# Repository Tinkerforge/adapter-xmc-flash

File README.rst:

XMC Flash Adapter
=================

This repository contains the firmware source code and the hardware design
files. The documentation generator configs can be found at
https://github.com/Tinkerforge/generators

Repository Content
------------------

software/:
 * examples/: Examples for all supported languages
 * build/: Makefile and compiled files
 * src/: Source code of firmware
 * generate_makefile: Shell script to generate Makefile from cmake script

hardware/:
 * Contains kicad project files and additionally schematics as pdf

datasheets/:
 * Contains datasheets for sensors and complex ICs that are used

Hardware
--------

The hardware is designed with the open source EDA Suite KiCad
(http://www.kicad.org). Before you are able to open the files,
you have to install the Tinkerforge kicad-libraries
(https://github.com/Tinkerforge/kicad-libraries). You can either clone
them directly in hardware/ or clone them in a separate folder and
symlink them into hardware/
(ln -s kicad_path/kicad-libraries project_path/hardware). After that you
can open the .pro file in hardware/ with kicad and from there view and
modify the schematics and the PCB layout.

Software
--------

To compile the c code we recommend you to install the newest CodeSourcery arm
eabi gcc compiler
(http://www.codesourcery.com/sgpp/lite/arm/portal/subscription?@template=lite).
You also need to install bricklib (https://github.com/Tinkerforge/bricklib)
and brickletlib (https://github.com/Tinkerforge/brickletlib).
You can either clone them directly in software/src/ or clone them in a
separate folder and symlink them into software/src/
(ln -s bricklib_path/bricklib project_path/software/src/).

After that you can generate a Makefile from the cmake script with the
generate_makefile shell script (in software/) and build the firmware
by invoking make in software/build/. The firmware (.bin) can then be found
in software/build/ and uploaded with brickv (click button "Flashing"
on start screen).

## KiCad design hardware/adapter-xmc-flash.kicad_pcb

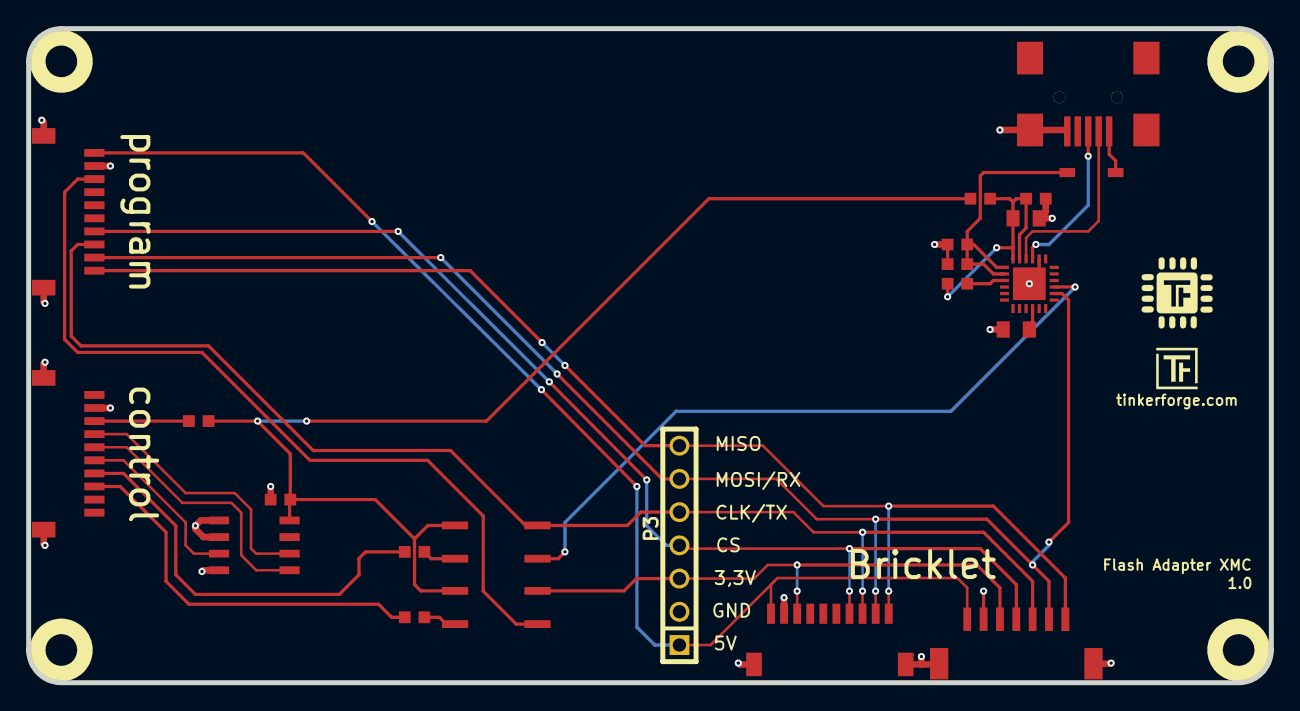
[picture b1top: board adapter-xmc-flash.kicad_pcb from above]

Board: 2 copper layers, 95.0 x 50.0 mm, 26 parts (0 on the bottom side), 25 nets.

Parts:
C1, C2, C5, C6: 100n; C0603F
C3, C4: 4.7µF/10V; C0805
D1: B0520LW; SOD-123
J1: USB-MINI-B-SMD
P1, P4, P5: CON-SENSOR
P2: CON-SENSOR2
P3: CONN_01X07; PIN_ARRAY-7X1
R1: 4k7; R0603F
R2: DNP; R0603F
R3: 0; R0603F
R4, R5: 1k; R0603F
U1: CP2104; QFN-24-4x4-EP
U2: M24C64; SOIC8
U3, U4: CPC1020N; SOP4-WIDE
U5, U6, U7, U8: DRILL; DRILL_NP

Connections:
3V3: C6.1, R2.1, R3.1, U2.8, U3.1, U4.1
GND: C1.2, C2.2, C3.2, C4.2, C5.2, C6.2, J1.5, J1.6, P1.2, P1.EP, P2.2, P2.EP, P3.2, P4.2, P4.EP, P5.2, P5.EP, U1.2, U1.25, U2.1, U2.2, U2.4
unnamed: C1.1, C2.1, D1.2, U1.7, U1.8
unnamed: C3.1, U1.16
unnamed: C4.1, C5.1, R1.1, R2.2, U1.5, U1.6
unnamed: D1.1, J1.1
unnamed: J1.2, U1.4
unnamed: J1.3, U1.3
unnamed: P1.1, P2.1, P3.1, P4.1
unnamed: P1.7, P2.4, P3.4, P4.7
unnamed: P1.10, P2.7, P3.7, P4.10
unnamed: P5.3, R3.2
unnamed: P5.4, U2.6
unnamed: P5.5, U2.5
unnamed: P5.6, U2.3
unnamed: P5.7, R4.2
unnamed: P5.8, R5.2
unnamed: R1.2, U1.9
unnamed: R4.1, U4.2
unnamed: R5.1, U3.2
POWER_RIN: P4.3, U3.3
POWER_ROUT: P1.3, P2.3, P3.3, U3.4
RXD: P1.9, P2.6, P3.6, P4.9, U1.20
TX_RIN: U1.21, U4.3
TX_ROUT: P1.8, P2.5, P3.5, P4.8, U4.4

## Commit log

2017-02-07 initial check in
2017-02-08 Add project file and schematic
2017-02-08 Add PCB layout
2017-02-08 Minor optical improvements
2017-02-08 PCB optimizations
2017-02-09 Add socket markings
2017-02-10 fix solid state footprints
2018-03-13 Assign footprints
2018-03-13 Minor adjustments
2018-03-13 Fix ground plane
2021-10-25 Update KiCad link
    https://www.kicad.org/blog/2021/10/Avoid-links-to-former-kicad-domain/

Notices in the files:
hardware/adapter-xmc-flash.kicad_pcb:
Licensed under CERN OHL v.1.1
Copyright (©) 2017, L.Lauer
Copyright Tinkerforge GmbH 2015.
This documentation describes Open Hardware and is licensed under the
CERN OHL v. 1.1.
